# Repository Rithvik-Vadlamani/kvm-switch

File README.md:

# HDMI/USB KVM switch

A four-layer board and STM32F030 firmware for sharing two HDMI displays and a four-port USB 2.0 hub between two computers. I designed the switching hardware and firmware, including supply supervision, hub reset control, and a timed disconnect sequence.

## Start here

- [Firmware and host-side tests](firmware/README.md)
- [Editable KiCad project](KVM_Switch.kicad_pro)
- [Prototype test plan](PROTOTYPE_TEST.md)
- [A2 verification results](verification-A2/Review-results.md)
- [Manufacturing notes](MANUFACTURING.md)

Current published design: A2, September 2026. It uses external regulated 12 V power. The USB-C host connectors carry USB 2.0 data; they do not provide USB-C video or USB Power Delivery.

The firmware switches with a 150 ms disconnect interval followed by 100 ms of settling, handles host detection, debounces the selection button, and uses watchdog recovery. The verification package contains state exploration and mutation results, plus PCB checks.

## Build and test

The firmware needs GNU Make and the GNU Arm toolchain. Run `make -C firmware` to build the STM32 image. The firmware README describes the host-side checks.

This is a prototype design. Firmware/model tests and static PCB checks do not establish USB enumeration, HDMI interoperability, signal integrity, or physical operating limits. The board has not been qualified on assembled hardware.

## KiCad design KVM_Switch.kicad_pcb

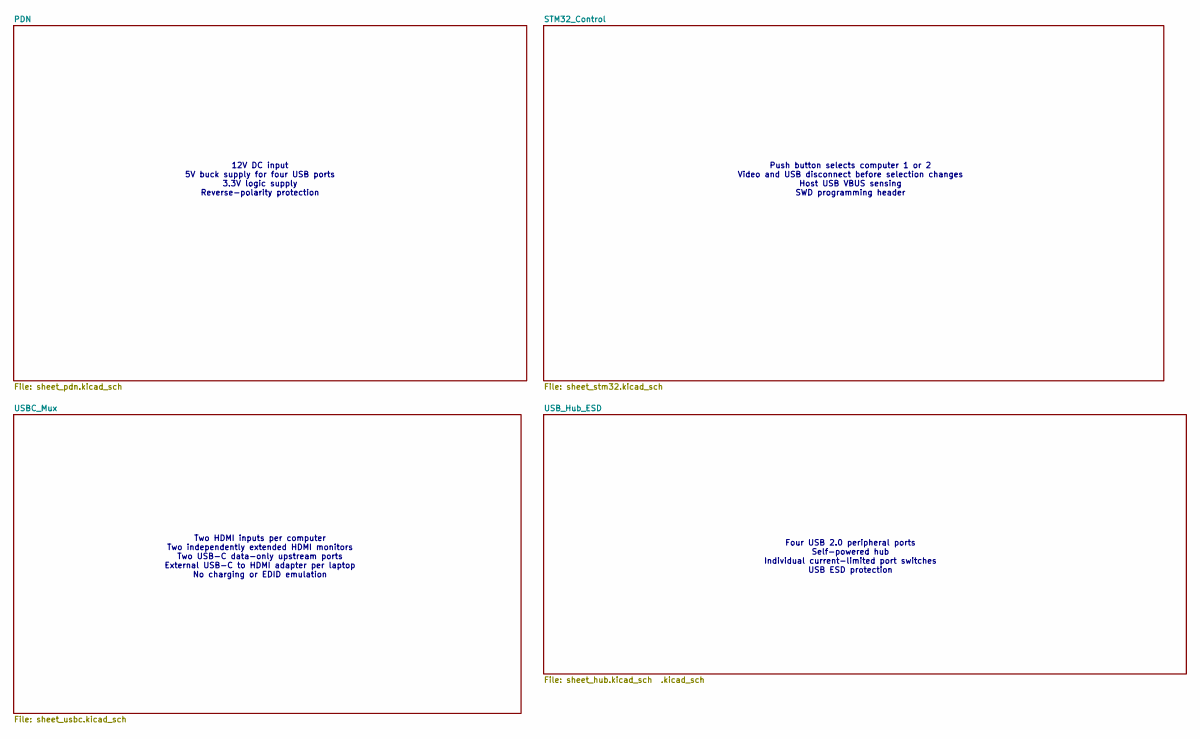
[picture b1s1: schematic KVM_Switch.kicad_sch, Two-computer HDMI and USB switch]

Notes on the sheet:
Four USB 2.0 peripheral ports Self-powered hub Individual current-limited port switches USB ESD protection
Two HDMI inputs per computer Two independently extended HDMI monitors Two USB-C data-only upstream ports External USB-C to HDMI adapter per laptop No charging or EDID emulation
Push button selects computer 1 or 2 Video and USB disconnect before selection changes Host USB VBUS sensing SWD programming header
12V DC input 5V buck supply for four USB ports 3.3V logic supply Reverse-polarity protection

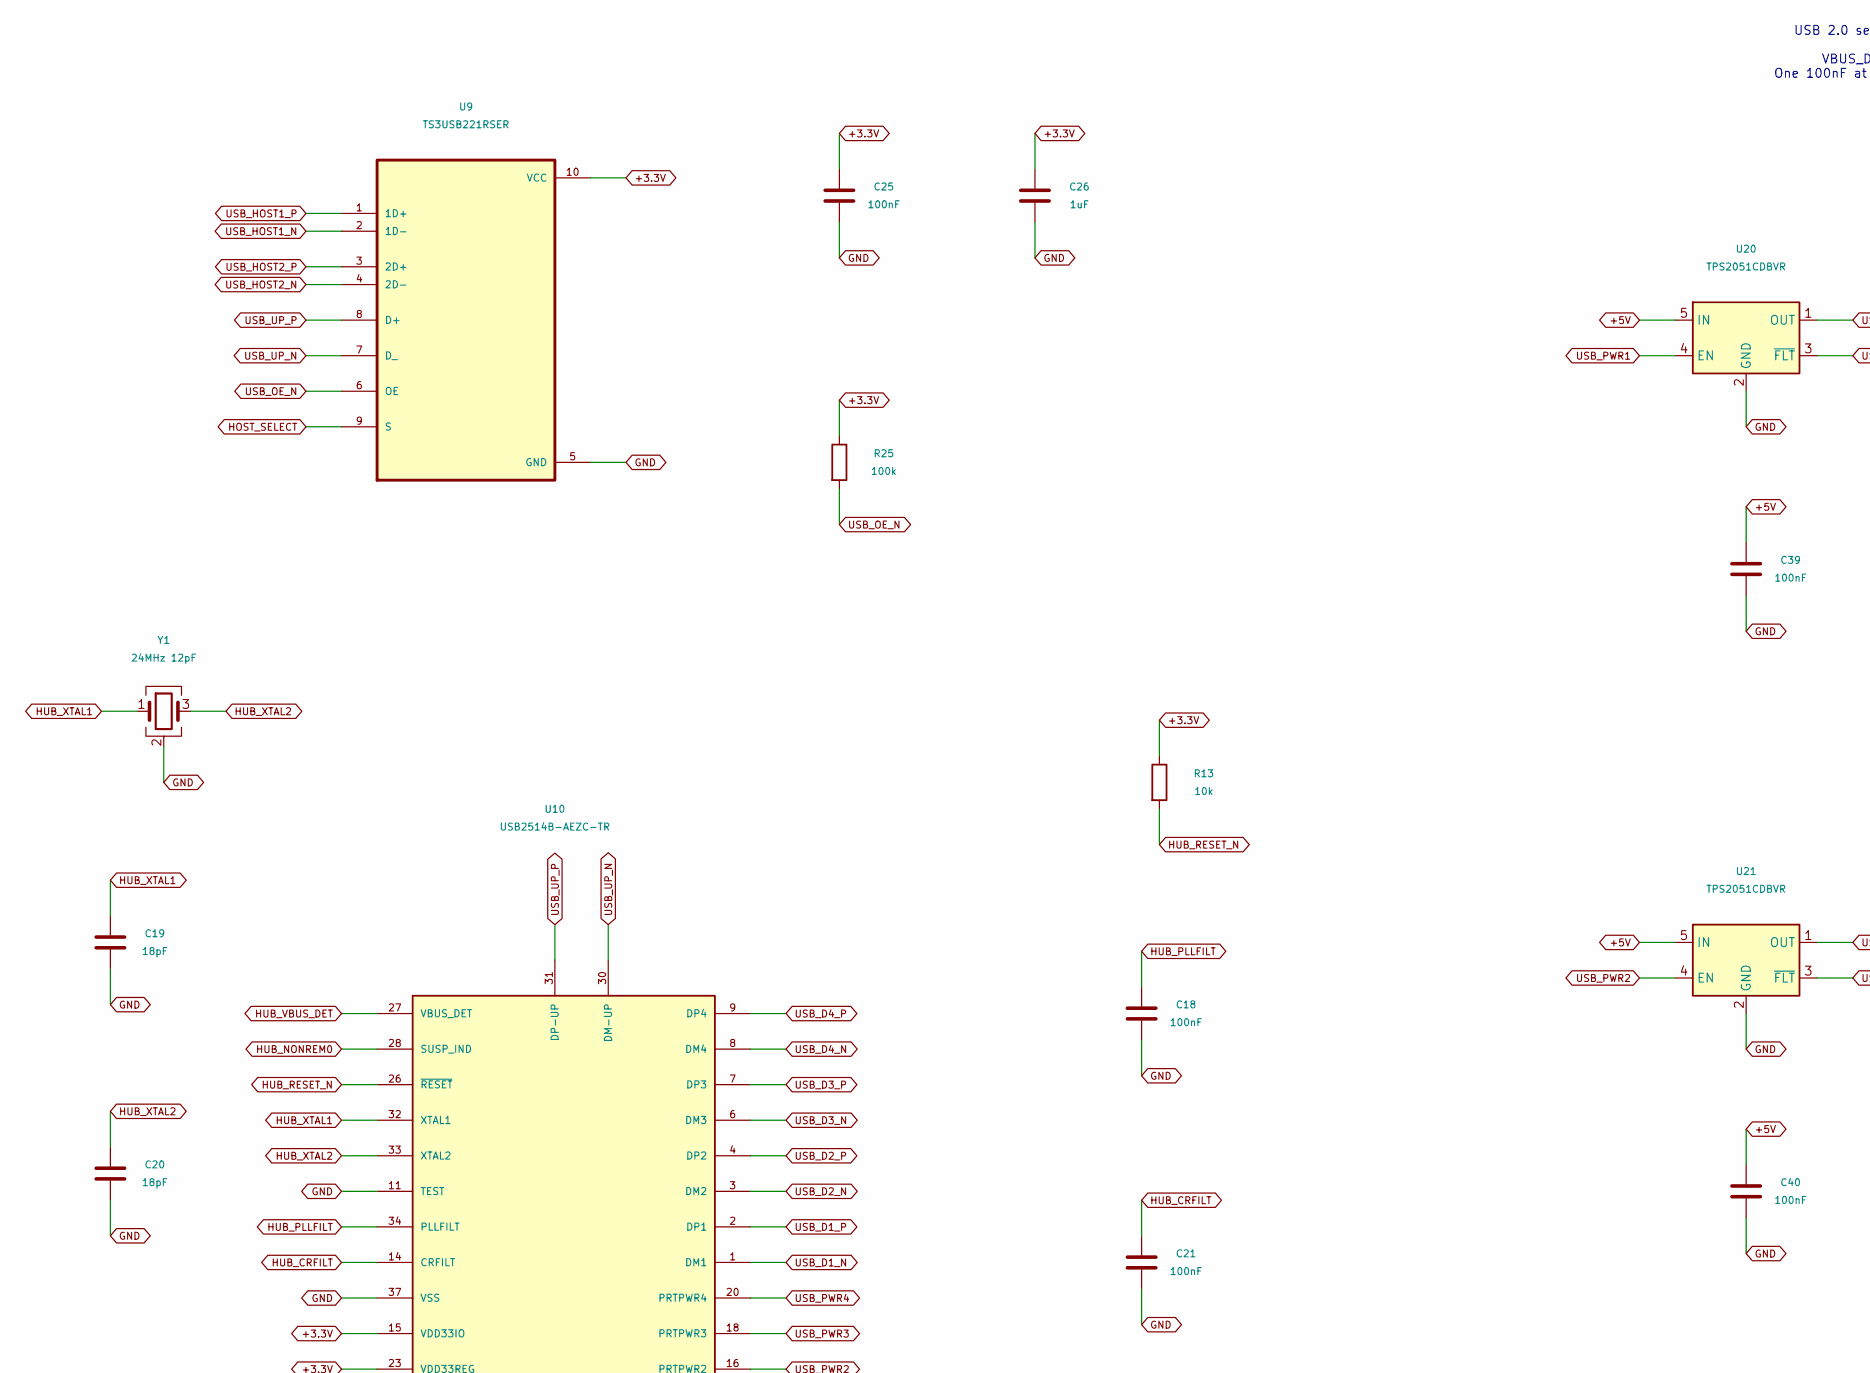
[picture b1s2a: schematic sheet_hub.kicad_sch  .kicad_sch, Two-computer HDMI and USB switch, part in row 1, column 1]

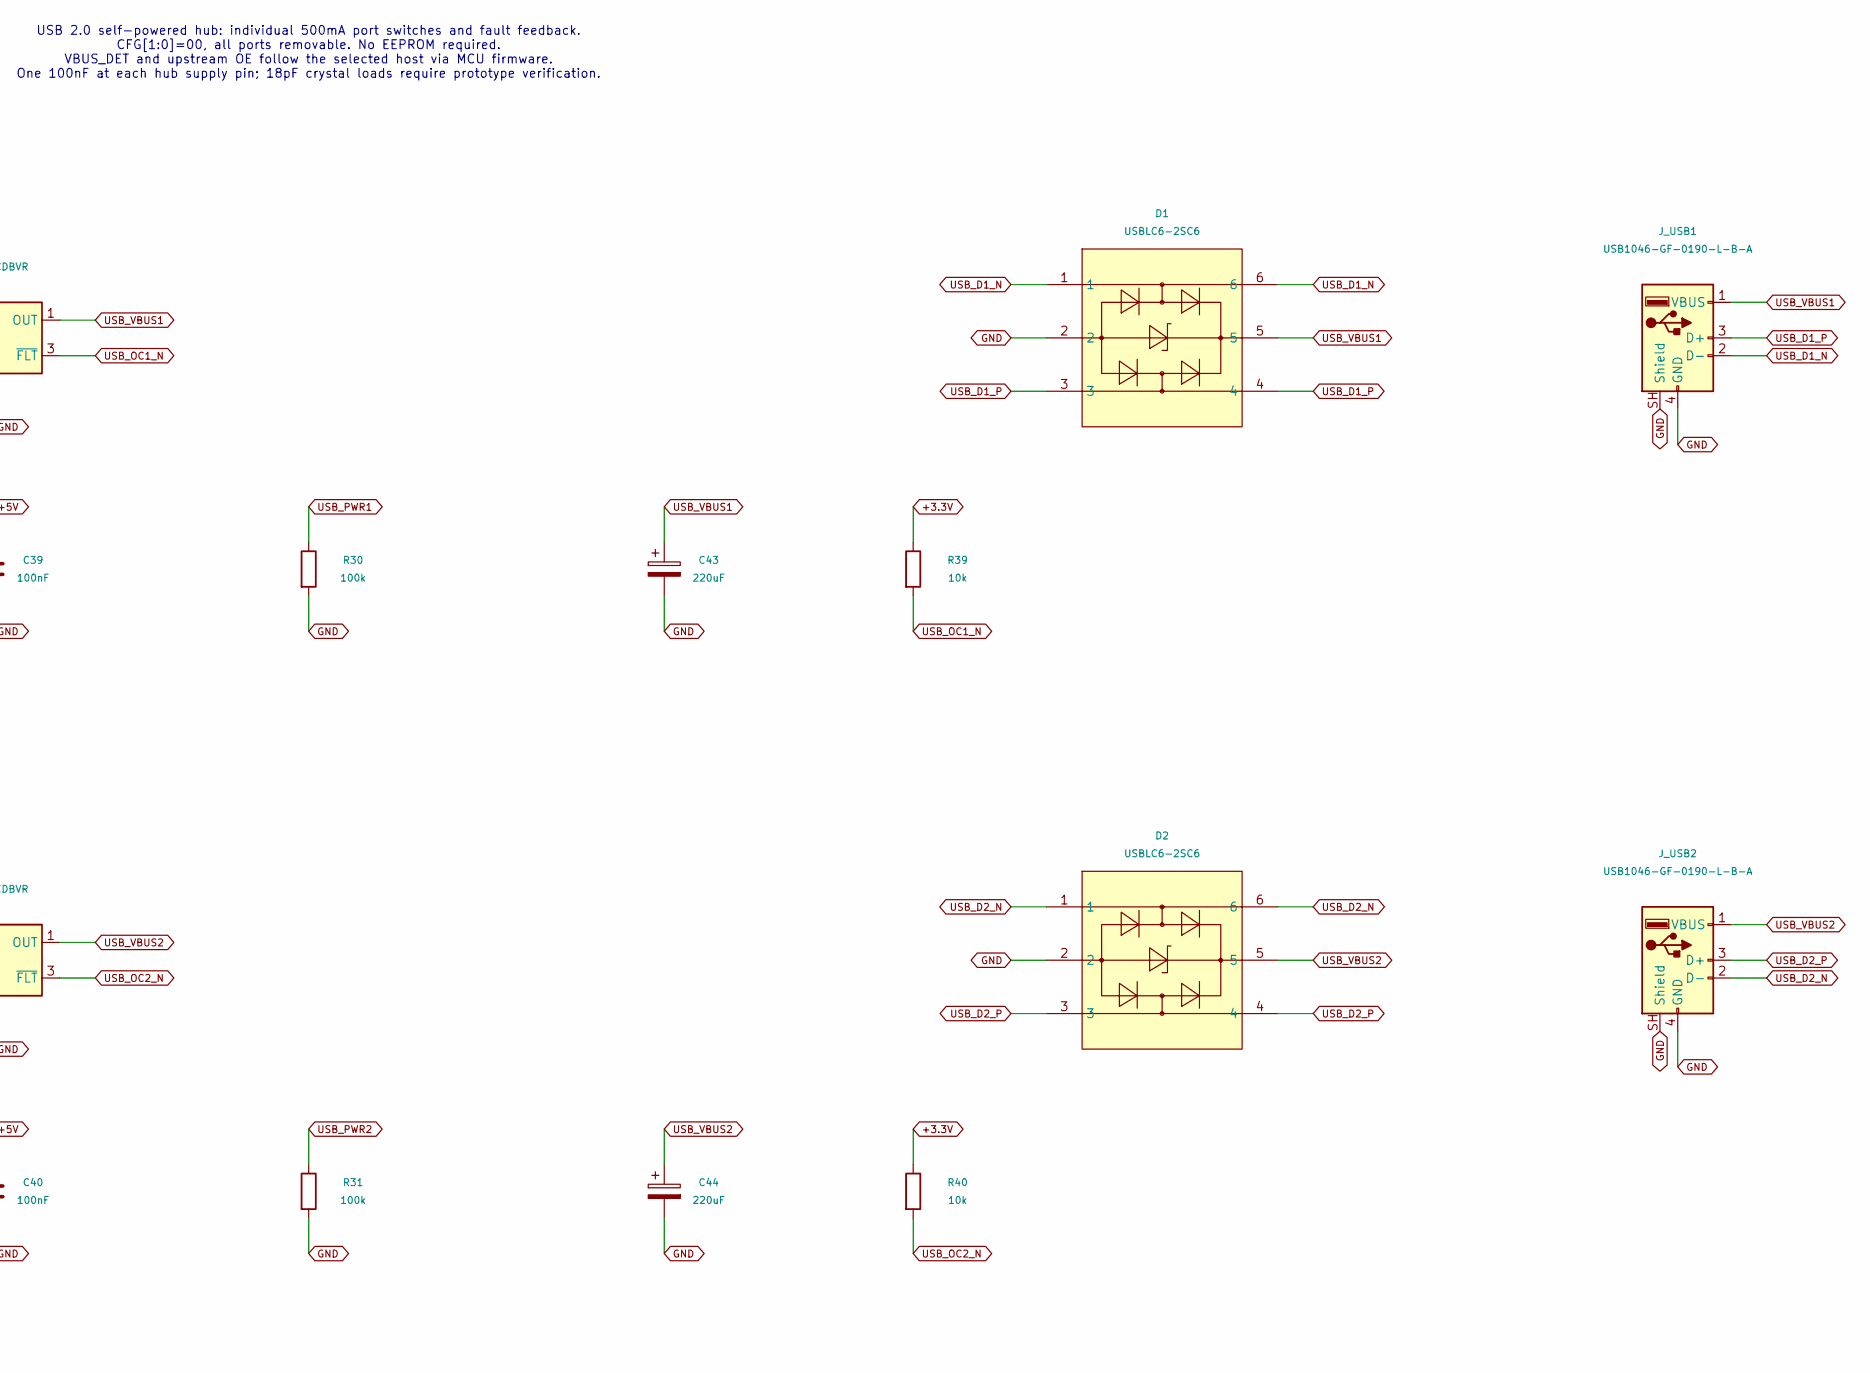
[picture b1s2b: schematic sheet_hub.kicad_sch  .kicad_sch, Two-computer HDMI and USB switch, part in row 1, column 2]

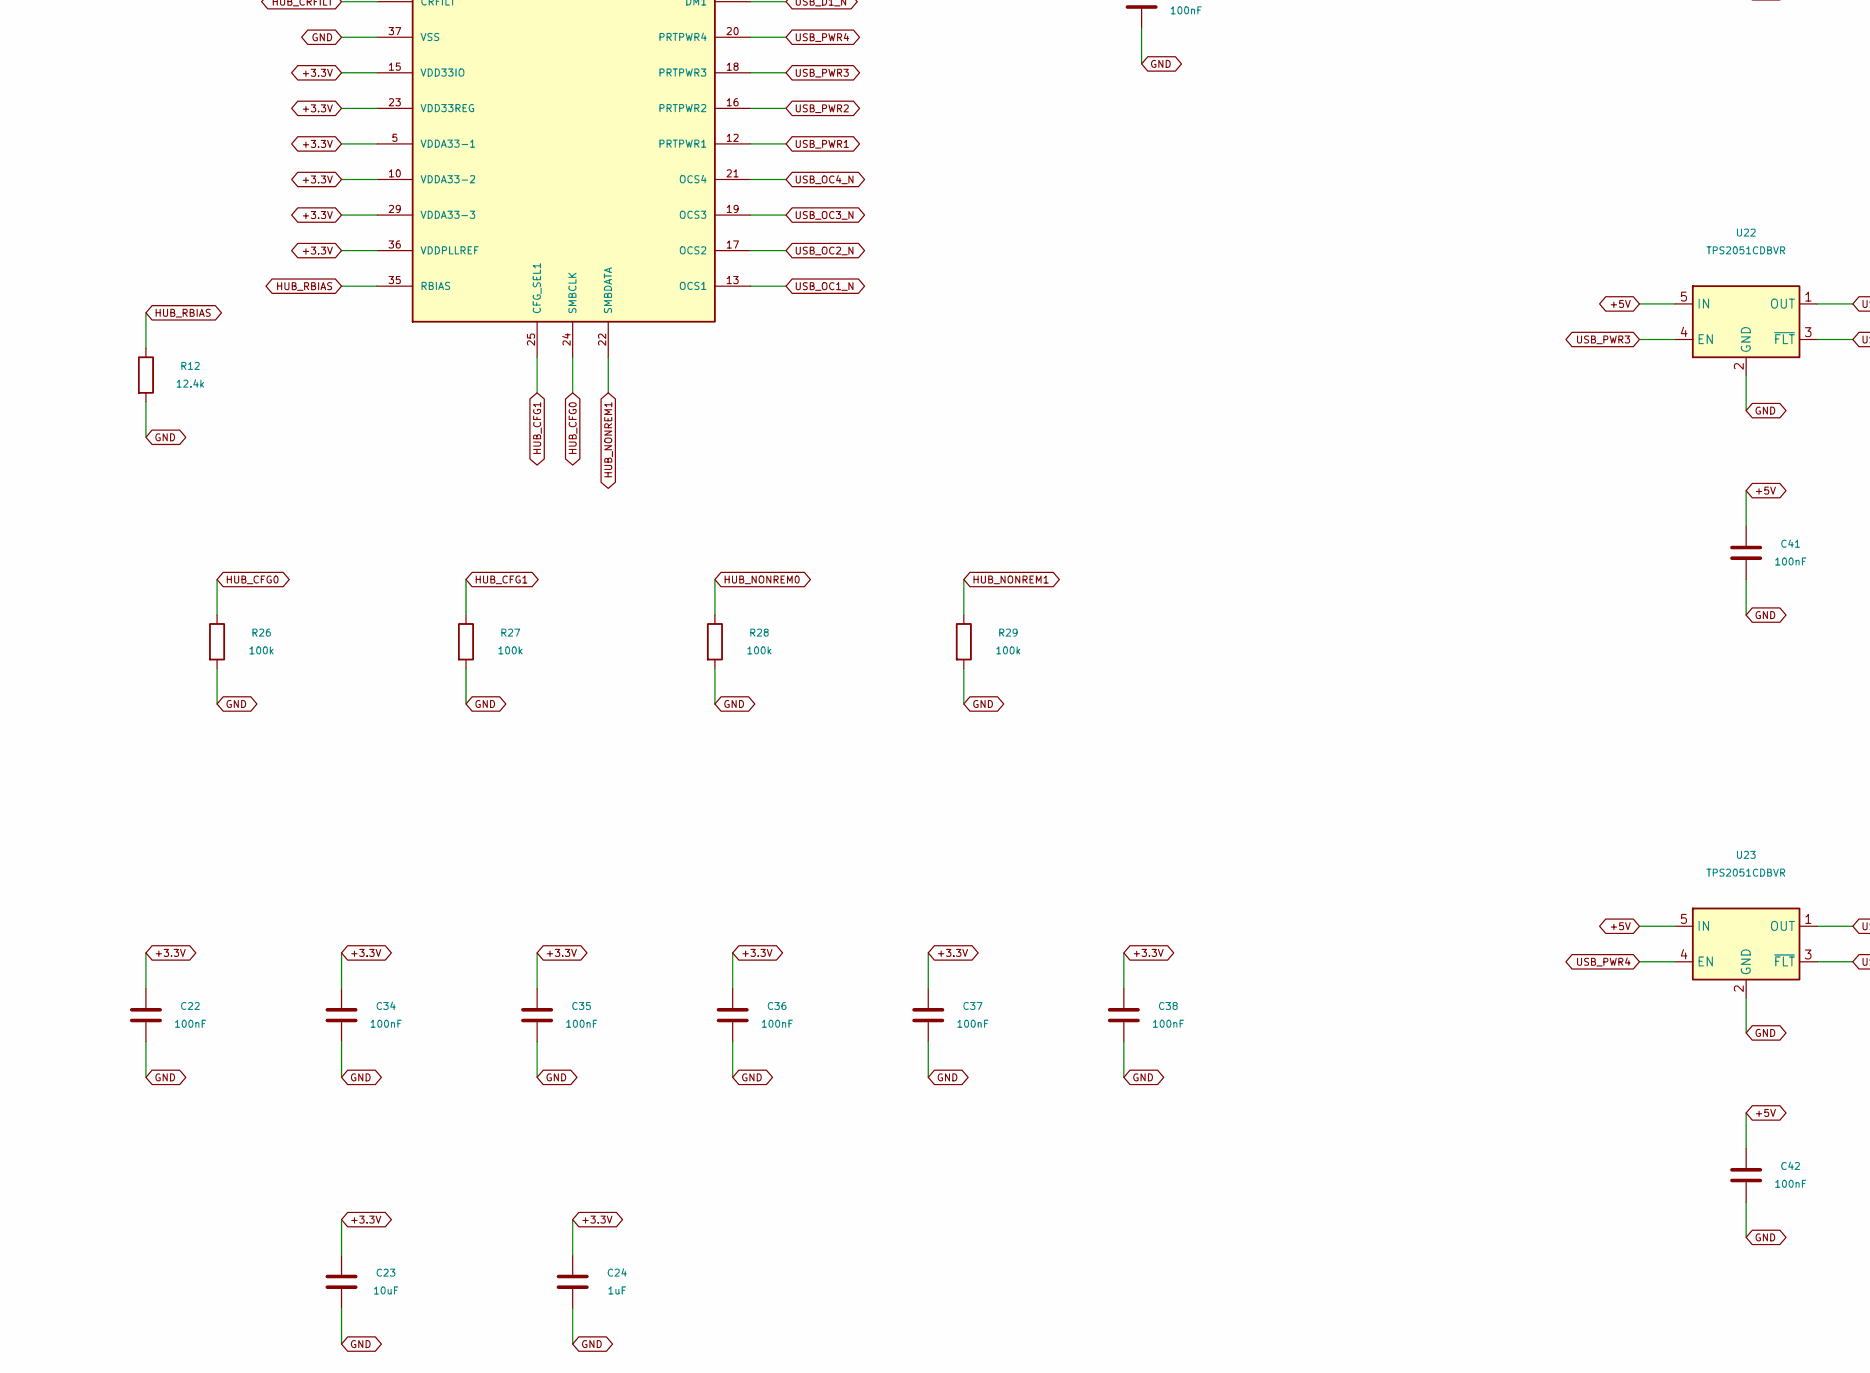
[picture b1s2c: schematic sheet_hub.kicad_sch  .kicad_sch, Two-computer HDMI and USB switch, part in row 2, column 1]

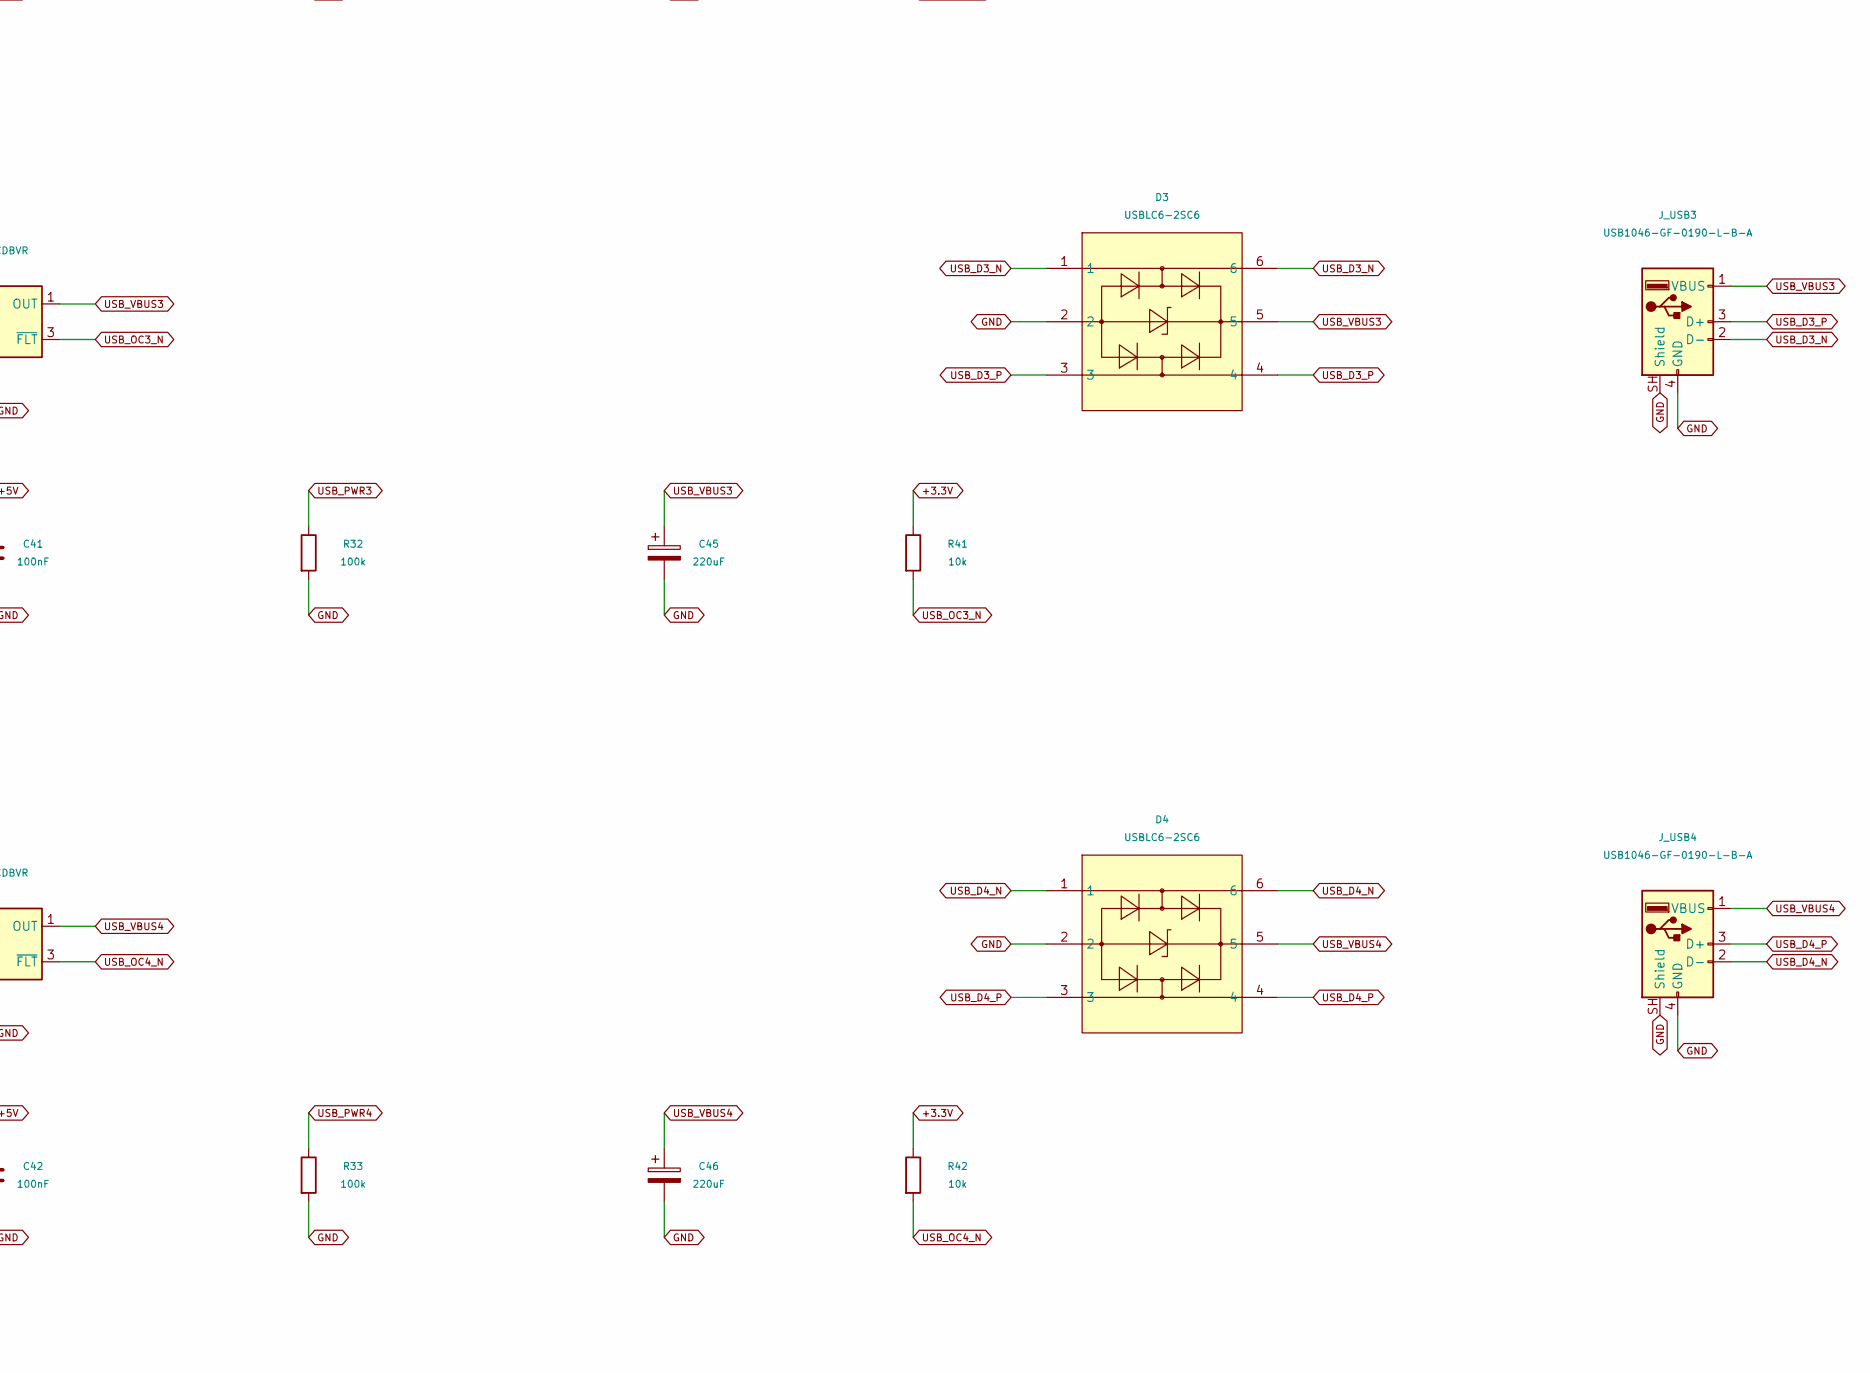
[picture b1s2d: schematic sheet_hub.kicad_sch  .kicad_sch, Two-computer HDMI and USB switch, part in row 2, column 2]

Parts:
C18: 100nF; C_0603_1608Metric; Voltage 50V; MPN CC0603KRX7R9BB104; LCSC Part C14663
C19, C20: 18pF; C_0402_1005Metric; Voltage 50V; MPN CGA2B2C0G1H180JT0Y0F; LCSC Part C76701
C21, C22, C25, C34, C35, C36, C37, C38, C39, C40, C41, C42: 100nF; C_0402_1005Metric; Voltage 50V; MPN CC0402KRX7R9BB104; LCSC Part C131394
C23: 10uF; C_0805_2012Metric; Voltage 16V; MPN CL21B106KOQNNNE; LCSC Part C95841
C24, C26: 1uF; C_0603_1608Metric; Voltage 16V; MPN CL10B105KO8NNNC; LCSC Part C59782
C43, C44, C45, C46: 220uF; CP_Elec_6.3x7.7; Voltage 10V; MPN UUD1A221MCL1GS; LCSC Part C445275
D1, D2, D3, D4: USBLC6-2SC6; SOT-23-6_L2.9-W1.6-P0.95-LS2.8-BL; MPN USBLC6-2SC6; LCSC Part C7519
J_USB1: USB1046-GF-0190-L-B-A; Assembly_J_USB1; MPN USB1046-GF-0190-L-B-A; LCSC Part C6307429
J_USB2: USB1046-GF-0190-L-B-A; Assembly_J_USB2; MPN USB1046-GF-0190-L-B-A; LCSC Part C6307429
J_USB3: USB1046-GF-0190-L-B-A; Assembly_J_USB3; MPN USB1046-GF-0190-L-B-A; LCSC Part C6307429
J_USB4: USB1046-GF-0190-L-B-A; Assembly_J_USB4; MPN USB1046-GF-0190-L-B-A; LCSC Part C6307429
R12: 12.4k; R_0402_1005Metric; Tolerance 1%; MPN 0402WGF1242TCE; LCSC Part C11692
R13, R39, R40, R41, R42: 10k; R_0402_1005Metric; Tolerance 1%; MPN 0402WGF1002TCE; LCSC Part C25744
R25, R26, R27, R28, R29, R30, R31, R32, R33: 100k; R_0402_1005Metric; Tolerance 1%; MPN 0402WGF1003TCE; LCSC Part C25741
U9: TS3USB221RSER; Texas_UQFN-10_1.5x2mm_P0.5mm; MPN TS3USB221RSER; LCSC Part C130085
U10: USB2514B-AEZC-TR; QFN-36-1EP_6x6mm_P0.5mm_EP3.7x3.7mm_ThermalVias; MPN USB2514B-AEZC-TR; LCSC Part C16251
U20, U21, U22, U23: TPS2051CDBVR; SOT-23-5; MPN TPS2051CDBVR; LCSC Part C129581
Y1: 24MHz 12pF; Assembly_Y1; MPN 3225 24M 12PF 10PPM; LCSC Part C5181479

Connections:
+3.3V: C22.1, C23.1, C24.1, C25.1, C26.1, C34.1, C35.1, C36.1, C37.1, C38.1, R13.1, R25.1, R39.1, R40.1, R41.1, R42.1, U9.10 (VCC), U10.5 (VDDA33-1), U10.10 (VDDA33-2), U10.15 (VDD33IO), U10.23 (VDD33REG), U10.29 (VDDA33-3), U10.36 (VDDPLLREF); also elsewhere on the board
+5V: C39.1, C40.1, C41.1, C42.1, U20.5 (IN), U21.5 (IN), U22.5 (IN), U23.5 (IN); also elsewhere on the board
GND: C18.2, C19.2, C20.2, C21.2, C22.2, C23.2, C24.2, C25.2, C26.2, C34.2, C35.2, C36.2, C37.2, C38.2, C39.2, C40.2, C41.2, C42.2, C43.2, C44.2, C45.2, C46.2, D1.2, D2.2, D3.2, D4.2, J_USB1.4 (GND), J_USB1.SH (Shield), J_USB2.4 (GND), J_USB2.SH (Shield), J_USB3.4 (GND), J_USB3.SH (Shield), J_USB4.4 (GND), J_USB4.SH (Shield), R12.2, R26.2, R27.2, R28.2, R29.2, R30.2, R31.2, R32.2, R33.2, U9.5 (GND), U10.11 (TEST), U10.37 (VSS), U20.2 (GND), U21.2 (GND), U22.2 (GND), U23.2 (GND), Y1.2 (G), Y1.4 (G); also elsewhere on the board
HOST_SELECT: U9.9 (S); also elsewhere on the board
HUB_CFG0: R26.1, U10.24 (SMBCLK)
HUB_CFG1: R27.1, U10.25 (CFG_SEL1)
HUB_CRFILT: C21.1, U10.14 (CRFILT)
HUB_NONREM0: R28.1, U10.28 (SUSP_IND)
HUB_NONREM1: R29.1, U10.22 (SMBDATA)
HUB_PLLFILT: C18.1, U10.34 (PLLFILT)
HUB_RBIAS: R12.1, U10.35 (RBIAS)
HUB_RESET_N: R13.2, U10.26 (~RESET); also elsewhere on the board
HUB_VBUS_DET: U10.27 (VBUS_DET); also elsewhere on the board
HUB_XTAL1: C19.1, U10.32 (XTAL1), Y1.1
HUB_XTAL2: C20.1, U10.33 (XTAL2), Y1.3
USB_D1_N: D1.1, D1.6, J_USB1.2 (D-), U10.1 (DM1)
USB_D1_P: D1.3, D1.4, J_USB1.3 (D+), U10.2 (DP1)
USB_D2_N: D2.1, D2.6, J_USB2.2 (D-), U10.3 (DM2)
USB_D2_P: D2.3, D2.4, J_USB2.3 (D+), U10.4 (DP2)
USB_D3_N: D3.1, D3.6, J_USB3.2 (D-), U10.6 (DM3)
USB_D3_P: D3.3, D3.4, J_USB3.3 (D+), U10.7 (DP3)
USB_D4_N: D4.1, D4.6, J_USB4.2 (D-), U10.8 (DM4)
USB_D4_P: D4.3, D4.4, J_USB4.3 (D+), U10.9 (DP4)
USB_HOST1_N: U9.2 (1D-); also elsewhere on the board
USB_HOST1_P: U9.1 (1D+); also elsewhere on the board
USB_HOST2_N: U9.4 (2D-); also elsewhere on the board
USB_HOST2_P: U9.3 (2D+); also elsewhere on the board
USB_OC1_N: R39.2, U10.13 (OCS1), U20.3 (~FLT)
USB_OC2_N: R40.2, U10.17 (OCS2), U21.3 (~FLT)
USB_OC3_N: R41.2, U10.19 (OCS3), U22.3 (~FLT)
USB_OC4_N: R42.2, U10.21 (OCS4), U23.3 (~FLT)
USB_OE_N: R25.2, U9.6 (OE); also elsewhere on the board
USB_PWR1: R30.1, U10.12 (PRTPWR1), U20.4 (EN)
USB_PWR2: R31.1, U10.16 (PRTPWR2), U21.4 (EN)
USB_PWR3: R32.1, U10.18 (PRTPWR3), U22.4 (EN)
USB_PWR4: R33.1, U10.20 (PRTPWR4), U23.4 (EN)
USB_UP_N: U9.7 (D_), U10.30 (DM-UP)
USB_UP_P: U9.8 (D+), U10.31 (DP-UP)
USB_VBUS1: C43.1, D1.5, J_USB1.1 (VBUS), U20.1 (OUT)
USB_VBUS2: C44.1, D2.5, J_USB2.1 (VBUS), U21.1 (OUT)
USB_VBUS3: C45.1, D3.5, J_USB3.1 (VBUS), U22.1 (OUT)
USB_VBUS4: C46.1, D4.5, J_USB4.1 (VBUS), U23.1 (OUT)

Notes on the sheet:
USB 2.0 self-powered hub: individual 500mA port switches and fault feedback. CFG[1:0]=00, all ports removable. No EEPROM required. VBUS_DET and upstream OE follow the selected host via MCU firmware. One 100nF at each hub supply pin; 18pF crystal loads require prototype verification.

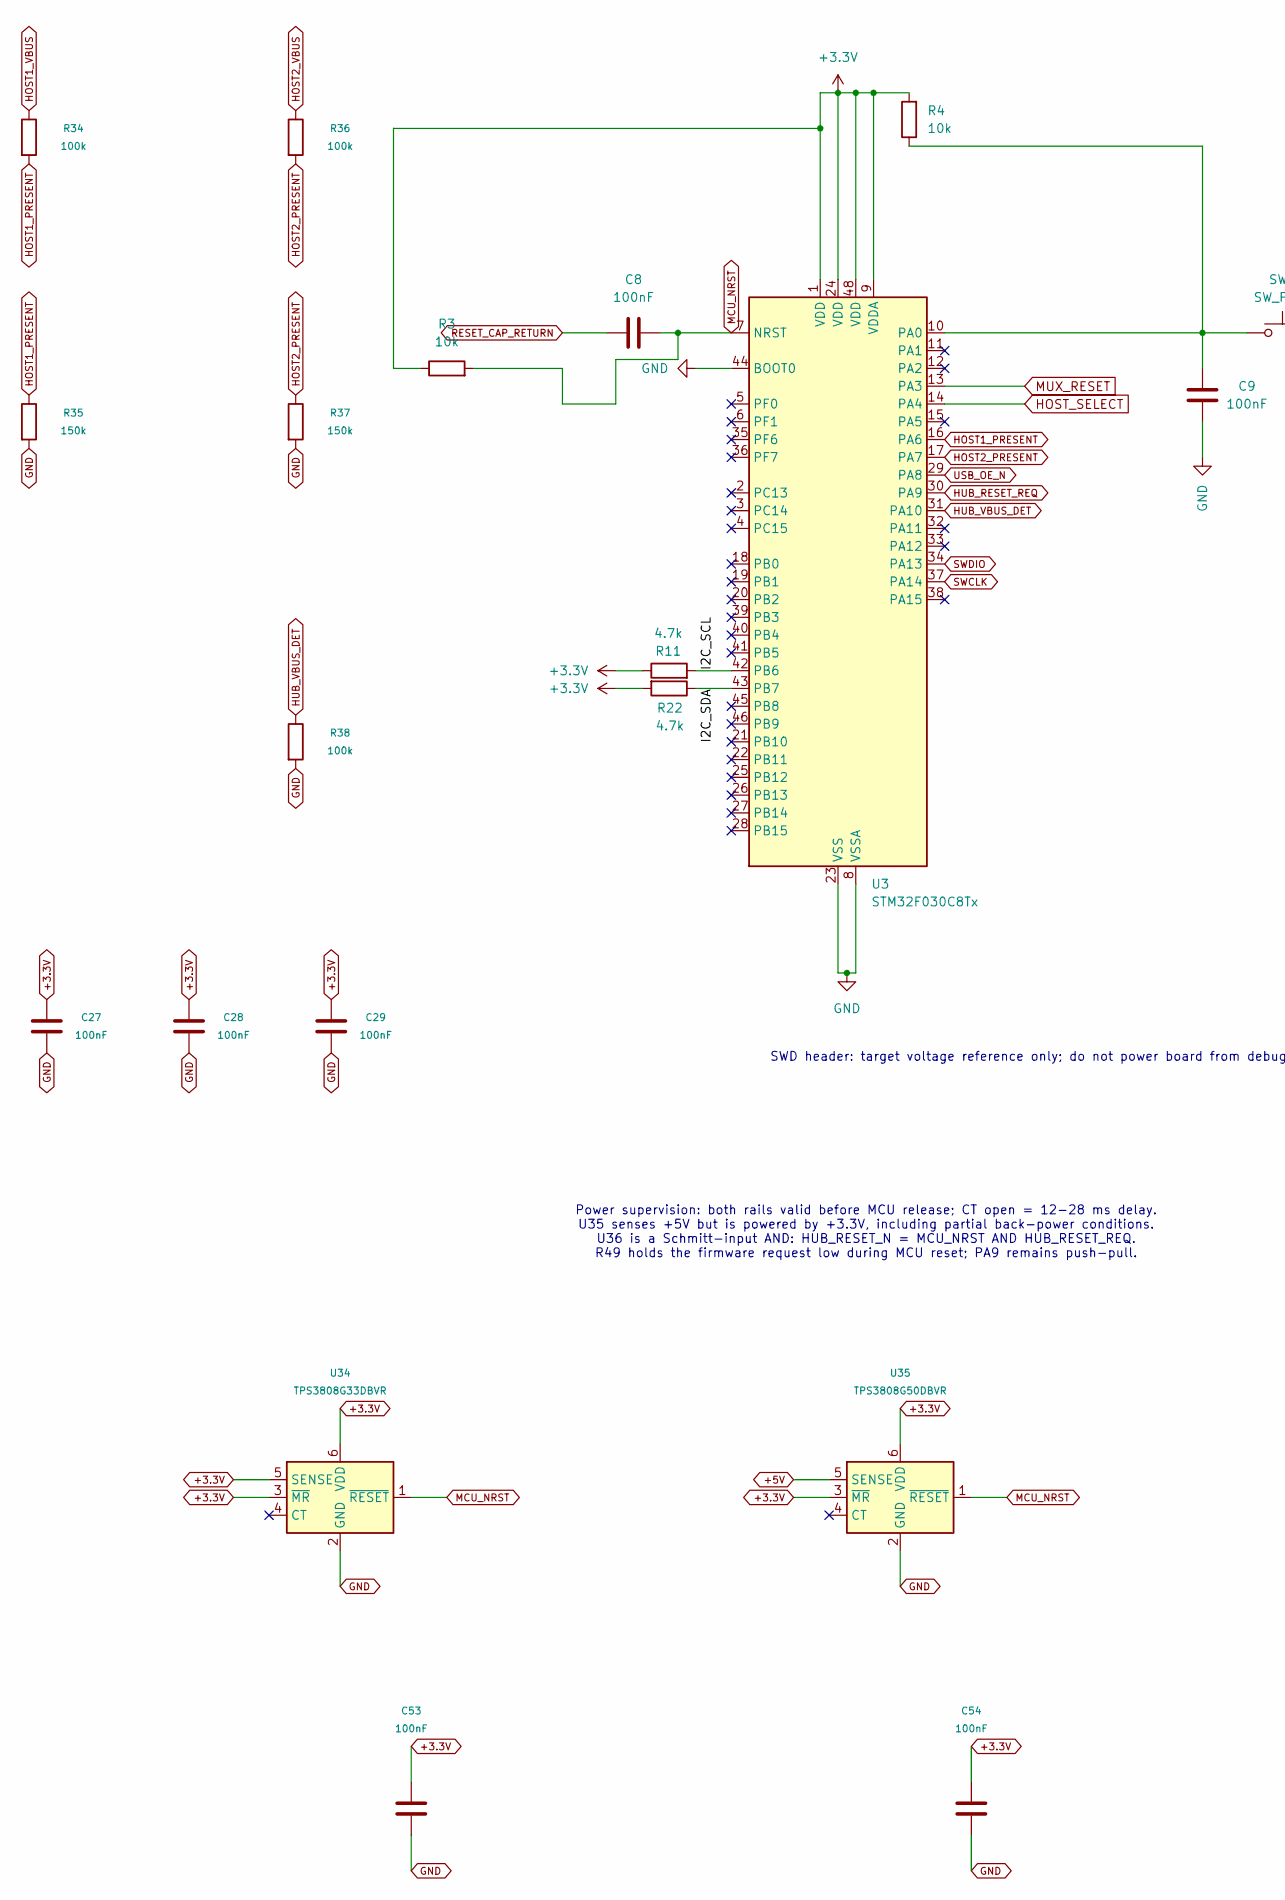
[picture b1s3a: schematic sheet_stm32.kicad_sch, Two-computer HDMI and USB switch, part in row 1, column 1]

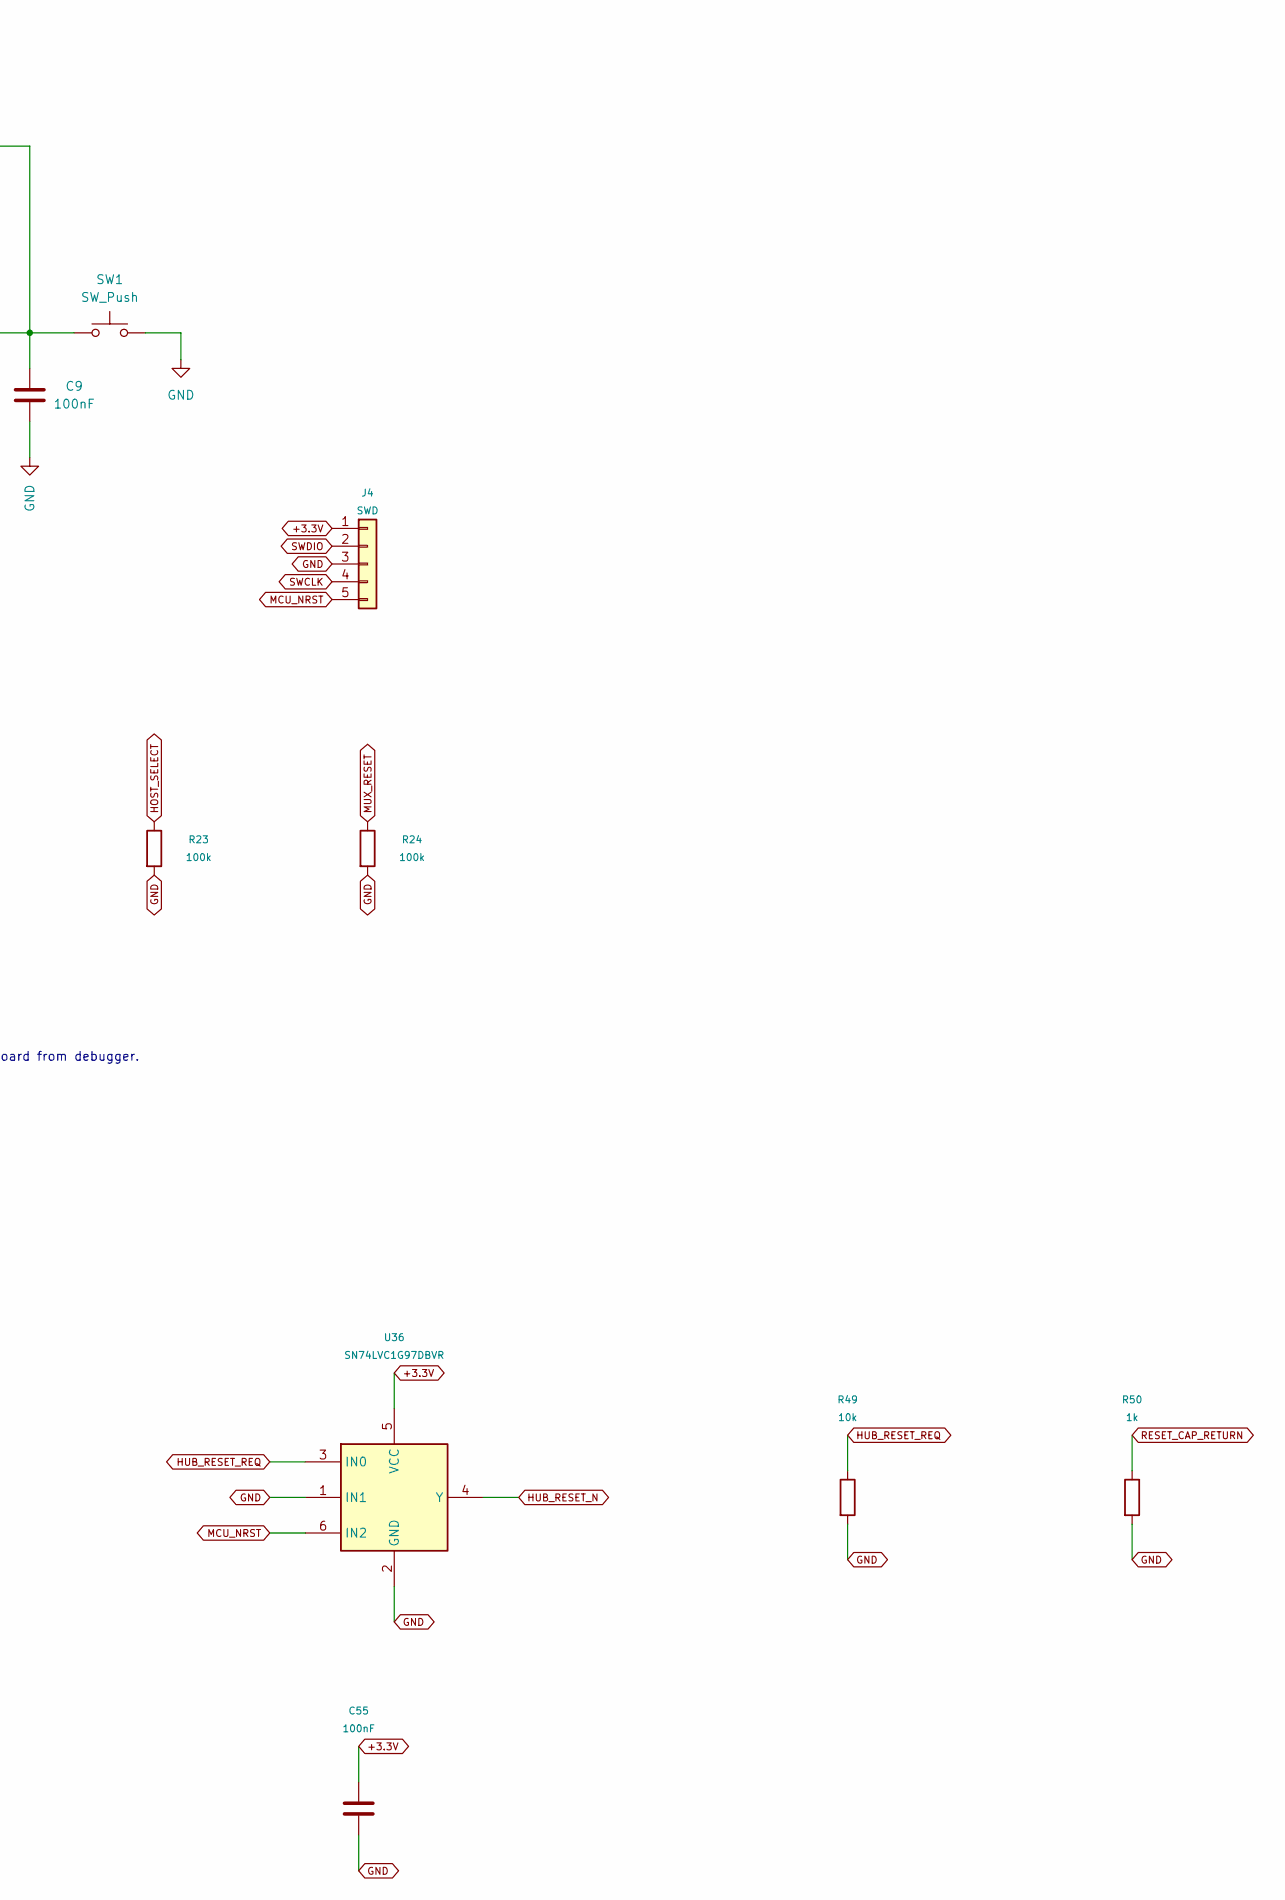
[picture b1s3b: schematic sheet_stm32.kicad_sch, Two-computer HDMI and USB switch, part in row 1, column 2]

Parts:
C8, C9, C27, C28, C29, C53, C54, C55: 100nF; C_0402_1005Metric; Voltage 50V; MPN CC0402KRX7R9BB104; LCSC Part C131394
J4: SWD; PinHeader_1x05_P2.54mm_Vertical; MPN PZ2.54-1X5P-H25; LCSC Part C42431812
R3, R4: 10k; R_0402_1005Metric; Tolerance 1%; MPN 0402WGF1002TCE; LCSC Part C25744
R11, R22: 4.7k; R_0402_1005Metric; Tolerance 1%; MPN 0402WGF4701TCE; LCSC Part C25900
R23, R24, R34, R36, R38: 100k; R_0402_1005Metric; Tolerance 1%; MPN 0402WGF1003TCE; LCSC Part C25741
R35, R37: 150k; R_0402_1005Metric; Tolerance 1%; MPN 0402WGF1503TCE; LCSC Part C25755
R49: 10k; R_0402_1005Metric; MPN 0402WGF1002TCE; LCSC Part C25744
R50: 1k; R_0402_1005Metric; MPN 0402WGF1001TCE; LCSC Part C11702
SW1: SW_Push; SW_SPST_Omron_B3F-40xx; MPN B3F-4050; LCSC Part C86707
U3: STM32F030C8Tx; LQFP-48_7x7mm_P0.5mm; MPN STM32F030C8T6; LCSC Part C23922
U34: TPS3808G33DBVR; SOT-23-6; MPN TPS3808G33DBVR; LCSC Part C43698
U35: TPS3808G50DBVR; SOT-23-6; MPN TPS3808G50DBVR; LCSC Part C134123
U36: SN74LVC1G97DBVR; SOT-23-6; MPN SN74LVC1G97DBVR; LCSC Part C128411

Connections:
+3.3V: C27.1, C28.1, C29.1, C53.1, C54.1, C55.1, J4.1, R3.1, R4.2, R11.1, R22.2, U3.1 (VDD), U3.9 (VDDA), U3.24 (VDD), U3.48 (VDD), U34.3 (~MR), U34.5 (SENSE), U34.6 (VDD), U35.3 (~MR), U35.6 (VDD), U36.5 (VCC); also elsewhere on the board
+5V: U35.5 (SENSE); also elsewhere on the board
/STM32_Control/I2C_SCL: R11.2, U3.42 (PB6)
/STM32_Control/I2C_SDA: R22.1, U3.43 (PB7)
GND: C9.2, C27.2, C28.2, C29.2, C53.2, C54.2, C55.2, J4.3, R23.2, R24.2, R35.2, R37.2, R38.2, R49.2, R50.2, SW1.2, U3.8 (VSSA), U3.23 (VSS), U3.44 (BOOT0), U3.47 (VSS), U34.2 (GND), U35.2 (GND), U36.1 (IN1), U36.2 (GND); also elsewhere on the board
HOST1_PRESENT: R34.2, R35.1, U3.16 (PA6)
HOST1_VBUS: R34.1; also elsewhere on the board
HOST2_PRESENT: R36.2, R37.1, U3.17 (PA7)
HOST2_VBUS: R36.1; also elsewhere on the board
HOST_SELECT: R23.1, U3.14 (PA4); also elsewhere on the board
HUB_RESET_N: U36.4 (Y); also elsewhere on the board
HUB_RESET_REQ: R49.1, U3.30 (PA9), U36.3 (IN0)
HUB_VBUS_DET: R38.1, U3.31 (PA10); also elsewhere on the board
MCU_NRST: C8.2, J4.5, R3.2, U3.7 (NRST), U34.1 (~RESET), U35.1 (~RESET), U36.6 (IN2)
MUX_RESET: R24.1, U3.13 (PA3); also elsewhere on the board
unnamed: C9.1, R4.1, SW1.1, U3.10 (PA0)
RESET_CAP_RETURN: C8.1, R50.1
SWCLK: J4.4, U3.37 (PA14)
SWDIO: J4.2, U3.34 (PA13)
USB_OE_N: U3.29 (PA8); also elsewhere on the board

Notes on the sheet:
SWD header: target voltage reference only; do not power board from debugger.
Power supervision: both rails valid before MCU release; CT open = 12-28 ms delay. U35 senses +5V but is powered by +3.3V, including partial back-power conditions. U36 is a Schmitt-input AND: HUB_RESET_N = MCU_NRST AND HUB_RESET_REQ. R49 holds the firmware request low during MCU reset; PA9 remains p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
